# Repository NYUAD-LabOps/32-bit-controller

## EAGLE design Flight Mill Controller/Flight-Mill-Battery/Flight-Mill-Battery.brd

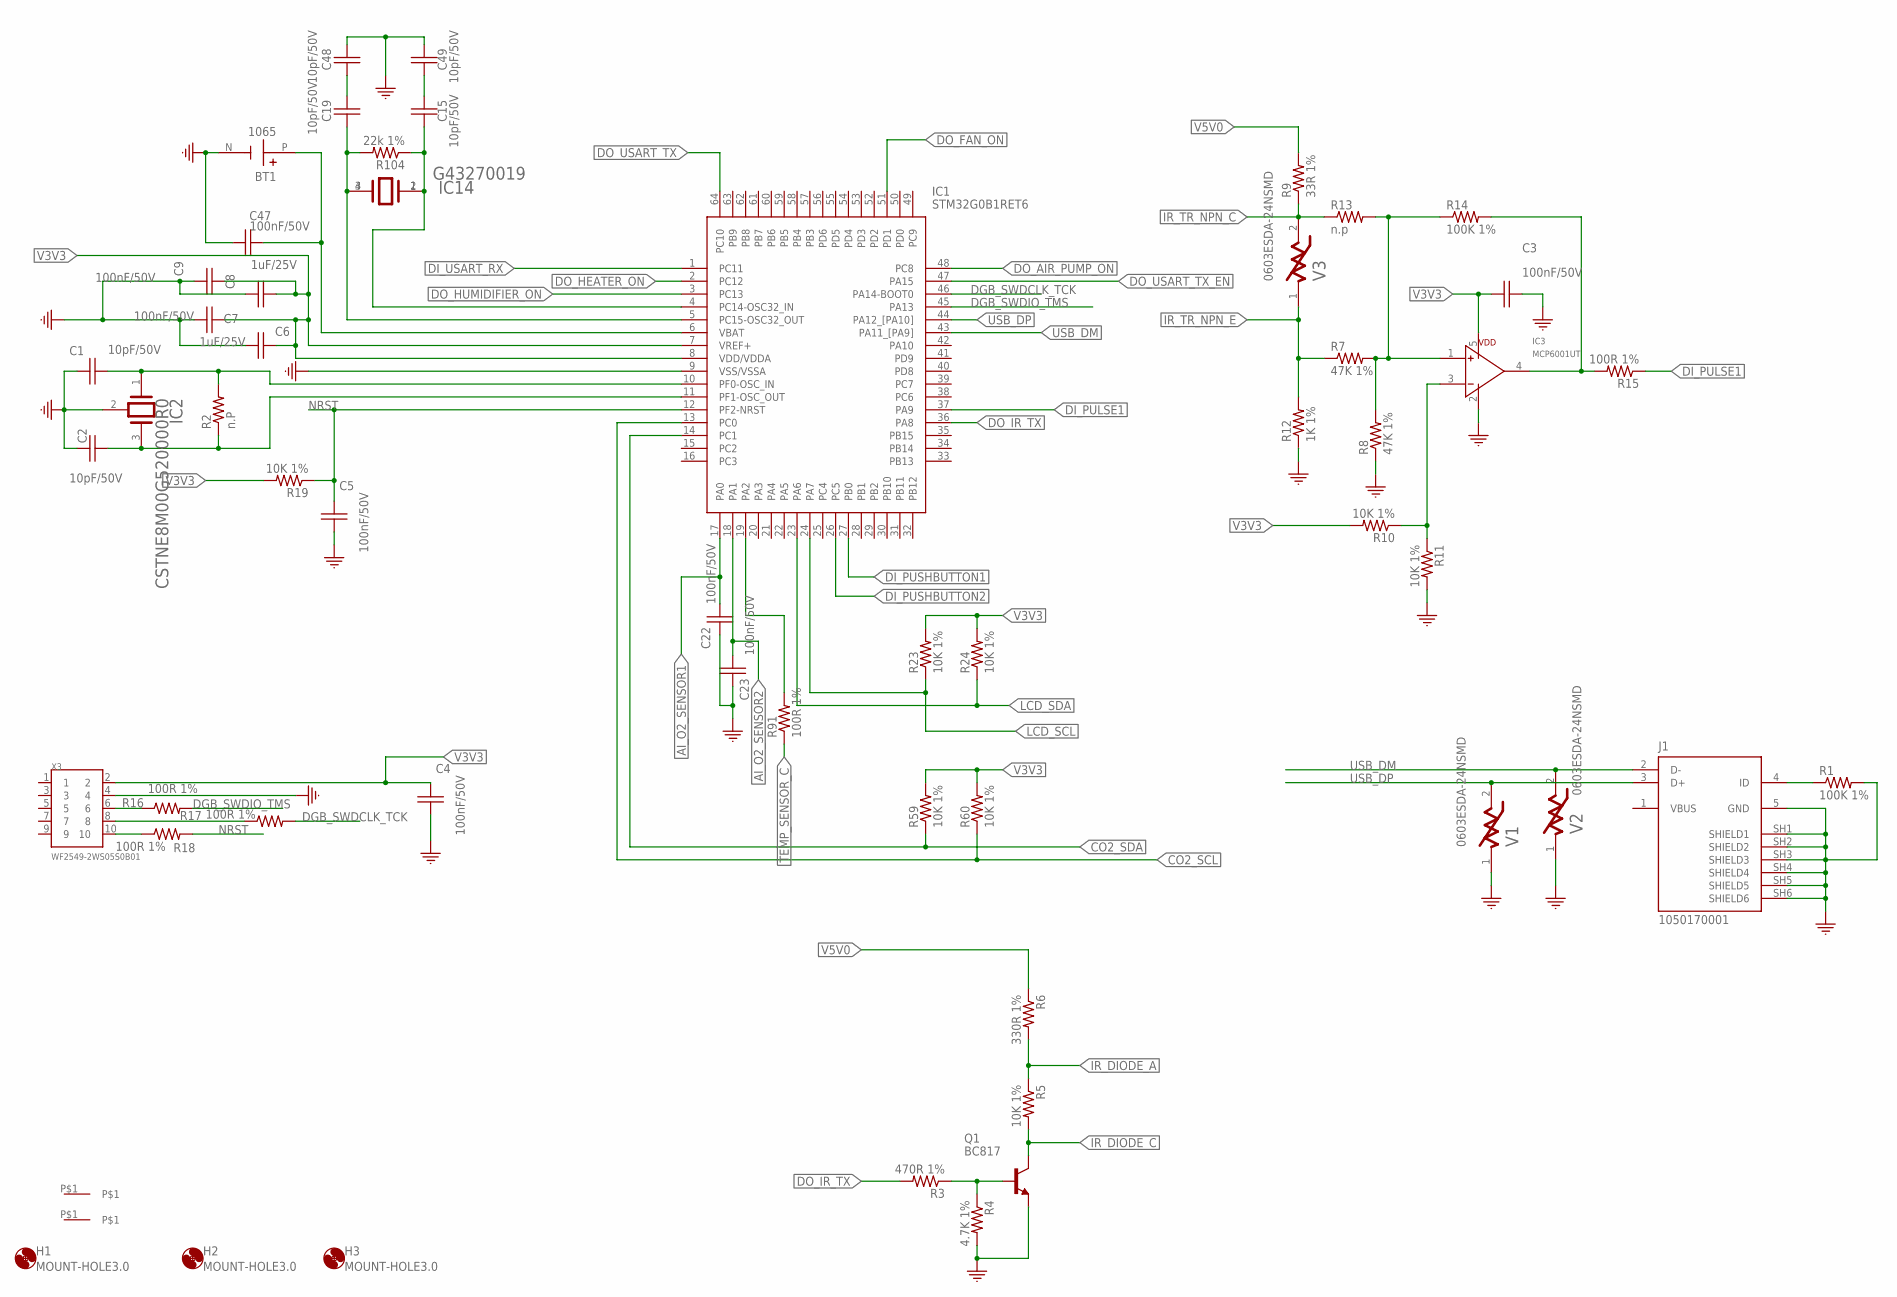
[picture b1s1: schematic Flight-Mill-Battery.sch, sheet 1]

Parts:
BT1: 1065; BAT_1065
C1, C2, C15, C19, C48, C49: 10pF/50V; EIA0603
C3, C4, C5, C7, C9, C22, C23, C47: 100nF/50V; EIA0603
C6, C8: 1uF/25V; EIA0603
FID1, FID2: FIDUCIAL
H1, H2, H3: MOUNT-HOLE3.0; 3,0
IC1: STM32G0B1RET6; QFP50P1200X1200X160-64N
IC2: CSTNE8M00G520000R0
IC3: MCP6001UT; SOT-23-5
IC14: G43270019
J1: 1050170001; MOLEX_1050170001
Q1: BC817; SOT23
R1, R14: 100K 1%; EIA0603
R2: n.P; EIA0603
R3: 470R 1%; EIA0603
R4: 4.7K 1%; EIA0603
R5, R10, R11, R19, R23, R24, R59, R60: 10K 1%; EIA0603
R6: 330R 1%; EIA0603
R7, R8: 47K 1%; EIA0603
R9: 33R 1%; EIA0603
R12: 1K 1%; EIA0603
R13: n.p; EIA0603
R15, R16, R17, R18, R91: 100R 1%; EIA0603
R104: 22k 1%; EIA0603
V1, V2, V3: 0603ESDA-24NSMD; EIA0603
X3: WF2549-2WS05S0B01; X10_100MIL_2XROW_VERT

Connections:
AI_O2_SENSOR1: C22.2, IC1.17 (PA0); also elsewhere on the board
AI_O2_SENSOR2: C23.2, IC1.18 (PA1); also elsewhere on the board
CO2_SCL: IC1.13 (PC0), R60.1; also elsewhere on the board
CO2_SDA: IC1.14 (PC1), R59.1; also elsewhere on the board
DGB_SWDCLK_TCK: IC1.46 (PA14-BOOT0), R17.2
DGB_SWDIO_TMS: IC1.45 (PA13), R16.2
DI_PULSE1: IC1.37 (PA9), R15.1
DI_PUSHBUTTON1: IC1.27 (PB0); also elsewhere on the board
DI_PUSHBUTTON2: IC1.26 (PC5); also elsewhere on the board
DI_USART_RX: IC1.1 (PC11); also elsewhere on the board
DO_AIR_PUMP_ON: IC1.48 (PC8); also elsewhere on the board
DO_FAN_ON: IC1.51 (PD1); also elsewhere on the board
DO_HEATER_ON: IC1.2 (PC12); also elsewhere on the board
DO_HUMIDIFIER_ON: IC1.3 (PC13); also elsewhere on the board
DO_IR_TX: IC1.36 (PA8), R3.2
DO_USART_TX: IC1.64 (PC10); also elsewhere on the board
DO_USART_TX_EN: IC1.47 (PA15); also elsewhere on the board
GND: BT1.N (NEG), C1.1, C2.1, C3.2, C4.1, C5.1, C6.2, C7.2, C8.2, C9.2, C22.1, C23.1, C47.2, C48.2, C49.2, IC1.9 (VSS/VSSA), IC2.2 (GND), IC3.2, J1.5 (GND), J1.SH1 (SHIELD1), J1.SH2 (SHIELD2), J1.SH3 (SHIELD3), J1.SH4 (SHIELD4), J1.SH5 (SHIELD5), J1.SH6 (SHIELD6), Q1.2 (E), R1.2, R4.2, R8.1, R11.2, R12.1, V1.1, V2.1, X3.4; also elsewhere on the board
IR_DIODE_A: R5.1, R6.2; also elsewhere on the board
IR_DIODE_C: Q1.3 (C), R5.2; also elsewhere on the board
IR_TR_NPN_C: R9.1, R13.1, V3.2; also elsewhere on the board
IR_TR_NPN_E: R7.1, R12.2, V3.1; also elsewhere on the board
LCD_SCL: IC1.24 (PA7), R23.1; also elsewhere on the board
LCD_SDA: IC1.23 (PA6), R24.1; also elsewhere on the board
unnamed: R16.1, X3.6
unnamed: C1.2, IC1.10 (PF0-OSC_IN), IC2.1 (INPUT), R2.2
unnamed: J1.4 (ID), R1.1
unnamed: C2.2, IC1.11 (PF1-OSC_OUT), IC2.3 (OUTPUT), R2.1
unnamed: IC3.1, R7.2, R8.2, R13.2, R14.1
unnamed: Q1.1 (B), R3.1, R4.1
unnamed: IC3.3, R10.1, R11.1
unnamed: IC3.4, R14.2, R15.2
unnamed: R17.1, X3.8
unnamed: R18.1, X3.10
unnamed: C19.2, C48.1
unnamed: IC1.19 (PA2), R91.2
unnamed: BT1.P (POS), C47.1, IC1.6 (VBAT)
unnamed: C19.1, IC1.5 (PC15-OSC32_OUT), IC14.3, IC14.4, R104.2
unnamed: C15.1, IC1.4 (PC14-OSC32_IN), IC14.1, IC14.2, R104.1
unnamed: C15.2, C49.1
NRST: C5.2, IC1.12 (PF2-NRST), R18.2, R19.1
TEMP_SENSOR_C: R91.1; also elsewhere on the board
USB_DM: IC1.43 (PA11_[PA9]), J1.2 (D-), V2.2
USB_DP: IC1.44 (PA12_[PA10]), J1.3 (D+), V1.2
V3V3: C3.1, C4.2, C6.1, C7.1, C8.1, C9.1, IC1.7 (VREF+), IC1.8 (VDD/VDDA), IC3.5, R10.2, R19.2, R23.2, R24.2, R59.2, R60.2, X3.2; also elsewhere on the board
V5V0: R6.1, R9.2; also elsewhere on the board
VBUS: J1.1 (VBUS)

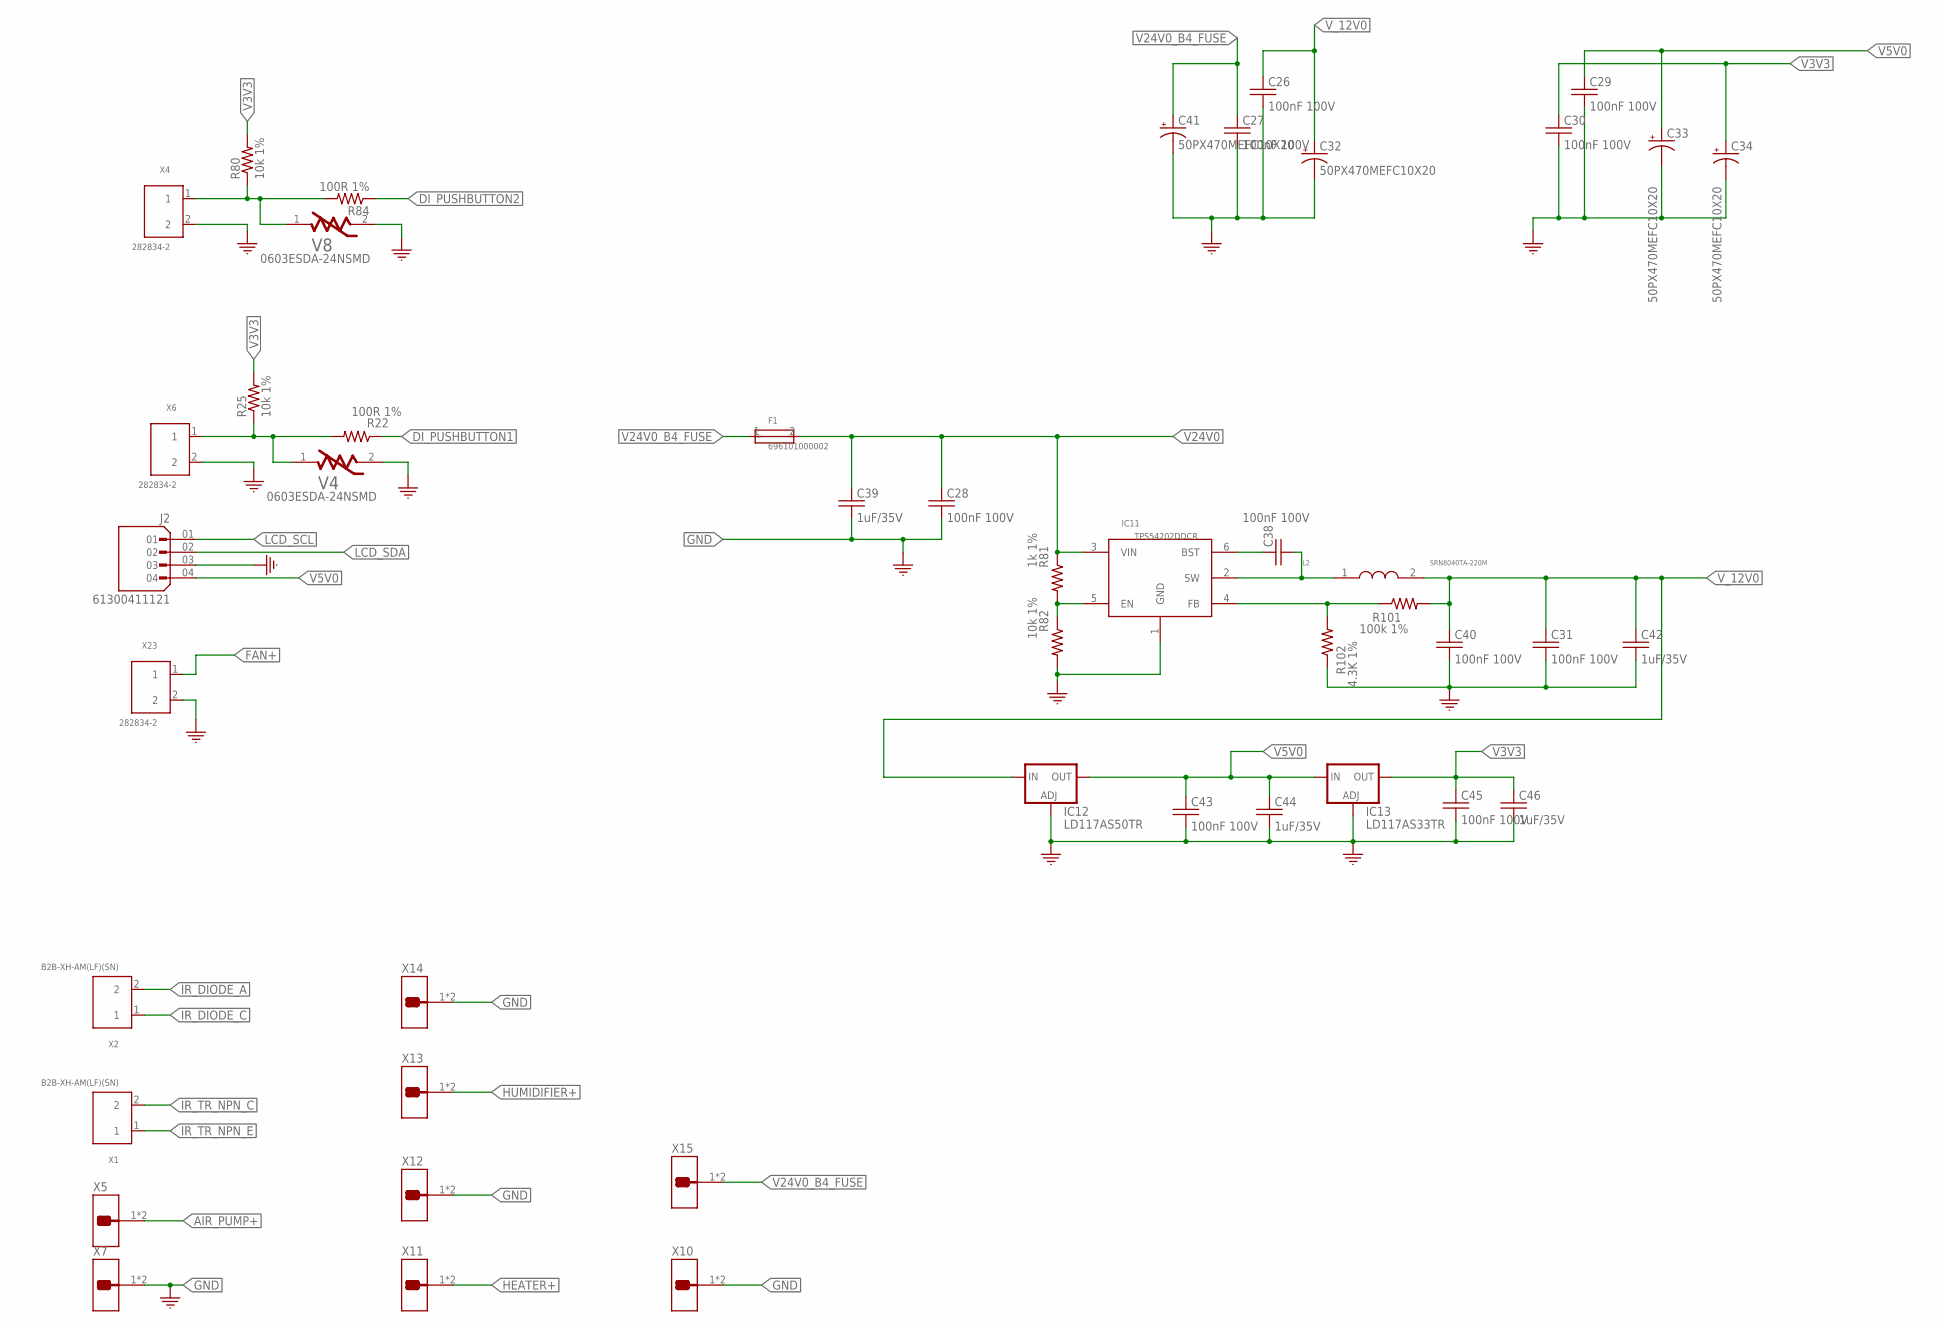
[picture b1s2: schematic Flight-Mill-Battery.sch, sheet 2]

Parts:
C26, C27, C28, C29, C30, C31, C38, C40, C43, C45: 100nF 100V; EIA0603
C32, C33, C34, C41: 50PX470MEFC10X20; CAPACITOR-ELKO-RM5-10X16
C39, C42, C44, C46: 1uF/35V; EIA0603
F1: 696101000002; FUSE_RM22.6
IC11: TPS54202DDCR; SOT23-6
IC12: LD117AS50TR; SOT223
IC13: LD117AS33TR; SOT223
J2: 61300411121; X04_100MIL_1ROW
L2: SRN8040TA-220M
R22, R84: 100R 1%; EIA0603
R25, R80, R82: 10k 1%; EIA0603
R81: 1k 1%; EIA0603
R101: 100k 1%; EIA0603
R102: 4.3K 1%; EIA0603
V4, V8: 0603ESDA-24NSMD; EIA0603
X1, X2: B2B-XH-AM(LF)(SN)
X4, X6, X23: 282834-2; TE_282834-2_0
X5, X7, X10, X11, X12, X13, X14, X15: 726386-2TE_726386-2; TE_726386-2

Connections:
AIR_PUMP+: X5.1, X5.1-2; also elsewhere on the board
DI_PUSHBUTTON1: R22.1; also elsewhere on the board
DI_PUSHBUTTON2: R84.1; also elsewhere on the board
FAN+: X23.1; also elsewhere on the board
GND: C26.2, C27.2, C28.2, C29.2, C30.2, C31.2, C32.2 (-), C33.2 (-), C34.2 (-), C39.2, C40.2, C41.2 (-), C42.2, C43.2, C44.2, C45.2, C46.2, IC11.1 (GND), IC12.1 (ADJ), IC13.1 (ADJ), J2.03, R82.2, R102.1, V4.2, V8.2, X4.2, X6.2, X7.1, X7.1-2, X10.1, X10.1-2, X12.1, X12.1-2, X14.1, X14.1-2, X23.2; also elsewhere on the board
HEATER+: X11.1, X11.1-2; also elsewhere on the board
HUMIDIFIER+: X13.1, X13.1-2; also elsewhere on the board
IR_DIODE_A: X2.2; also elsewhere on the board
IR_DIODE_C: X2.1; also elsewhere on the board
IR_TR_NPN_C: X1.2; also elsewhere on the board
IR_TR_NPN_E: X1.1; also elsewhere on the board
LCD_SCL: J2.01; also elsewhere on the board
LCD_SDA: J2.02; also elsewhere on the board
unnamed: IC11.5 (EN), R81.2, R82.1
unnamed: R22.2, R25.1, V4.1, X6.1
unnamed: R80.1, R84.2, V8.1, X4.1
unnamed: C38.1, IC11.6 (BST)
unnamed: C38.2, IC11.2 (SW), L2.1
unnamed: IC11.4 (FB), R101.1, R102.2
V3V3: C30.1, C34.1 (+), C45.1, C46.1, IC13.4 (OUT), R25.2, R80.2; also elsewhere on the board
V5V0: C29.1, C33.1 (+), C43.1, C44.1, IC12.4 (OUT), IC13.3 (IN), J2.04; also elsewhere on the board
V24V0: C28.1, C39.1, F1.2, IC11.3 (VIN), R81.1; also elsewhere on the board
V24V0_B4_FUSE: C27.1, C41.1 (+), F1.1, X15.1, X15.1-2
V_12V0: C26.1, C31.1, C32.1 (+), C40.1, C42.1, IC12.3 (IN), L2.2, R101.2; also elsewhere on the board

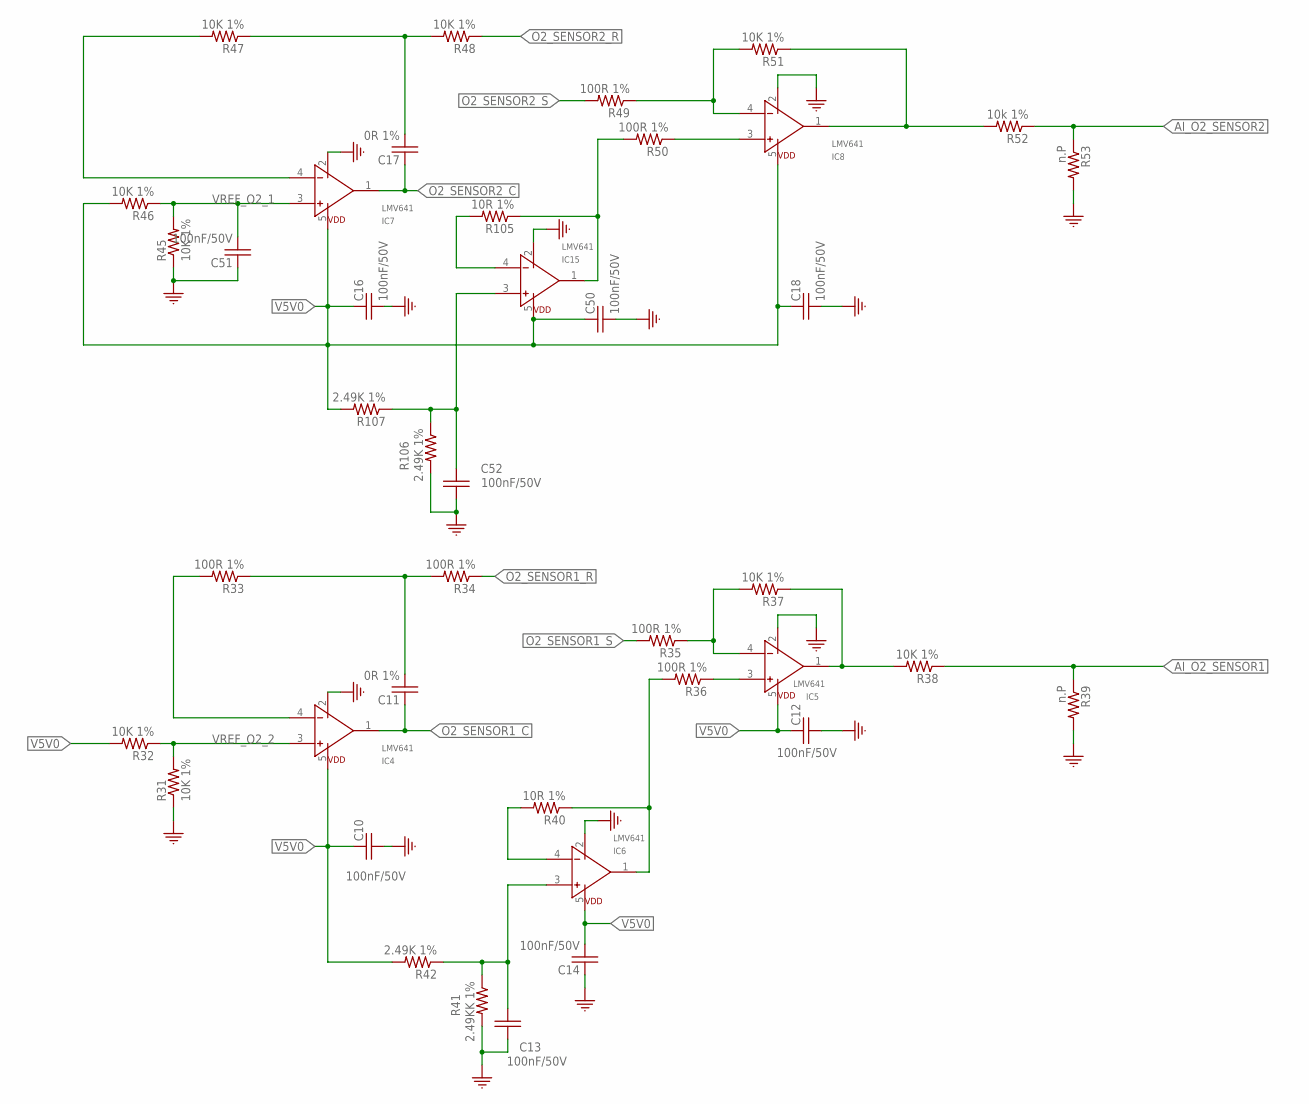
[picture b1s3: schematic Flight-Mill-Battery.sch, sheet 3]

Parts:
C10, C12, C13, C14, C16, C18, C50, C51, C52: 100nF/50V; EIA0603
C11, C17: 0R 1%; EIA0603
IC4, IC5, IC6, IC7, IC8, IC15: LMV641; SOT-23-5
R31, R32, R37, R38, R45, R46, R47, R48, R51: 10K 1%; EIA0603
R33, R34, R35, R36, R49, R50: 100R 1%; EIA0603
R39, R53: n.P; EIA0603
R40, R105: 10R 1%; EIA0603
R41: 2.49KK 1%; EIA0603
R42, R106, R107: 2.49K 1%; EIA0603
R52: 10k 1%; EIA0603

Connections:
AI_O2_SENSOR: IC5.1 (OUT), R37.1, R38.2
AI_O2_SENSOR1: R38.1, R39.1; also elsewhere on the board
AI_O2_SENSOR2: R52.1, R53.1; also elsewhere on the board
GND: C10.2, C12.2, C13.1, C14.1, C16.2, C18.2, C50.2, C51.1, C52.1, IC4.2 (VEE), IC5.2 (VEE), IC6.2 (VEE), IC7.2 (VEE), IC8.2 (VEE), IC15.2 (VEE), R31.1, R39.2, R41.2, R45.1, R53.2, R106.2; also elsewhere on the board
unnamed: IC5.4 (IN-), R35.1, R37.2
unnamed: IC6.4 (IN-), R40.2
unnamed: C11.2, R33.1, R34.2
unnamed: IC4.4 (IN-), R33.2
unnamed: IC6.1 (OUT), R36.2, R40.1
unnamed: IC5.3 (IN+), R36.1
unnamed: C13.2, IC6.3 (IN+), R41.1, R42.1
unnamed: C17.2, R47.1, R48.2
unnamed: IC7.4 (IN-), R47.2
unnamed: IC8.4 (IN-), R49.1, R51.2
unnamed: C52.2, IC15.3 (IN+), R106.1, R107.1
unnamed: IC8.1 (OUT), R51.1, R52.2
unnamed: IC15.4 (IN-), R105.2
unnamed: IC15.1 (OUT), R50.2, R105.1
unnamed: IC8.3 (IN+), R50.1
O2_SENSOR1_C: C11.1, IC4.1 (OUT); also elsewhere on the board
O2_SENSOR1_R: R34.1; also elsewhere on the board
O2_SENSOR1_S: R35.2; also elsewhere on the board
O2_SENSOR2_C: C17.1, IC7.1 (OUT); also elsewhere on the board
O2_SENSOR2_R: R48.1; also elsewhere on the board
O2_SENSOR2_S: R49.2; also elsewhere on the board
V5V0: C10.1, C12.1, C14.2, C16.1, C18.1, C50.1, IC4.5 (VCC), IC5.5 (VCC), IC6.5 (VCC), IC7.5 (VCC), IC8.5 (VCC), IC15.5 (VCC), R32.2, R42.2, R46.2, R107.2; also elsewhere on the board
VREF_O2_1: C51.2, IC7.3 (IN+), R45.2, R46.1
VREF_O2_2: IC4.3 (IN+), R31.2, R32.1

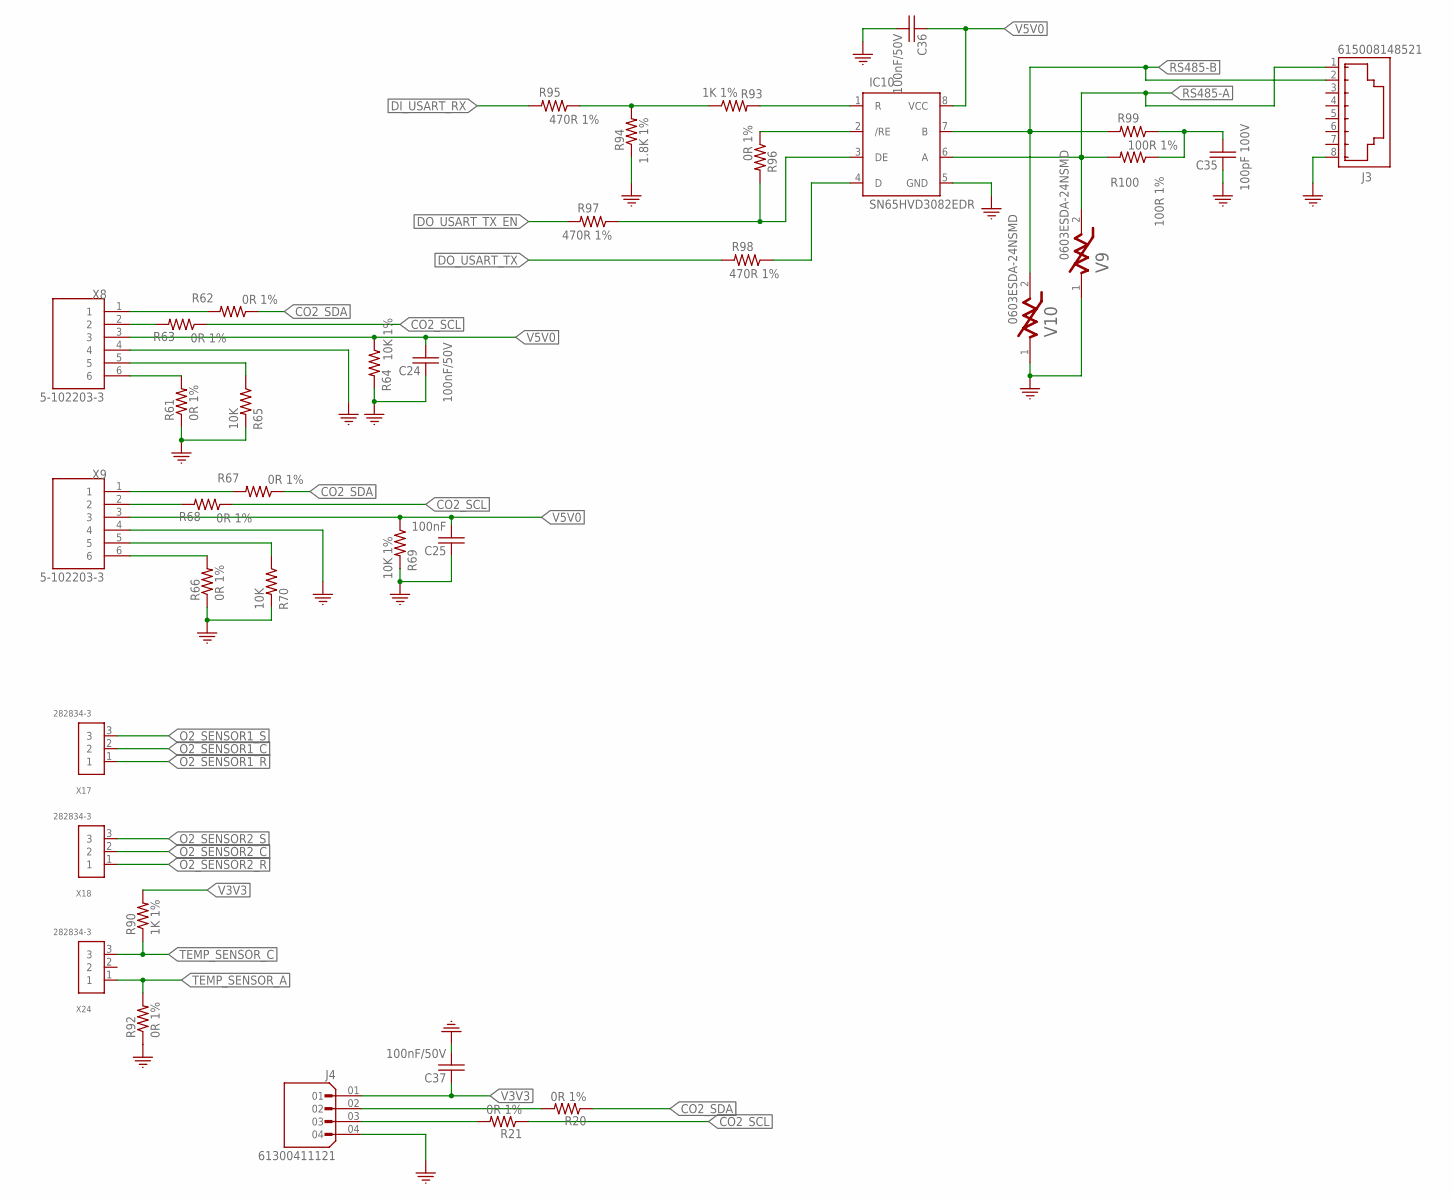
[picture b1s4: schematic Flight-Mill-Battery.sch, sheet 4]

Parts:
C24, C36, C37: 100nF/50V; EIA0603
C25: 100nF; EIA0603
C35: 100pF 100V; EIA0603
IC10: SN65HVD3082EDR; SOIC8
J3: 615008148521
J4: 61300411121; X04_100MIL_1ROW
R20, R21, R61, R62, R63, R66, R67, R68, R92, R96: 0R 1%; EIA0603
R64, R69: 10K 1%; EIA0603
R65, R70: 10K; EIA0603
R90, R93: 1K 1%; EIA0603
R94: 1.8K 1%; EIA0603
R95, R97, R98: 470R 1%; EIA0603
R99, R100: 100R 1%; EIA0603
V9, V10: 0603ESDA-24NSMD; EIA0603
X8, X9: 5-102203-3; TE_5-102203-3
X17, X18, X24: 282834-3; TE_282834-3_0

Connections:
CO2_SCL: R21.1, R63.1, R68.1; also elsewhere on the board
CO2_SDA: R20.1, R62.1, R67.1; also elsewhere on the board
DI_USART_RX: R95.2; also elsewhere on the board
DO_USART_TX: R98.2; also elsewhere on the board
DO_USART_TX_EN: R97.2; also elsewhere on the board
GND: C24.1, C25.1, C35.1, C36.2, C37.2, IC10.5 (GND), J3.8, J4.04, R61.1, R64.2, R65.2, R66.1, R69.2, R70.2, R92.1, R94.1, V9.1, V10.1, X8.4, X9.4; also elsewhere on the board
unnamed: R61.2, X8.6
unnamed: R62.2, X8.1
unnamed: R63.2, X8.2
unnamed: R65.1, X8.5
unnamed: R66.2, X9.6
unnamed: R67.2, X9.1
unnamed: R68.2, X9.2
unnamed: R70.1, X9.5
unnamed: R93.1, R94.2, R95.1
unnamed: IC10.1 (R), R93.2
unnamed: IC10.2 (/RE), R96.1
unnamed: IC10.3 (DE), R96.2, R97.1
unnamed: IC10.4 (D), R98.1
unnamed: J4.02, R20.2
unnamed: J4.03, R21.2
unnamed: C35.2, R99.1, R100.1
O2_SENSOR1_C: X17.2; also elsewhere on the board
O2_SENSOR1_R: X17.1; also elsewhere on the board
O2_SENSOR1_S: X17.3; also elsewhere on the board
O2_SENSOR2_C: X18.2; also elsewhere on the board
O2_SENSOR2_R: X18.1; also elsewhere on the board
O2_SENSOR2_S: X18.3; also elsewhere on the board
RS485-A: IC10.6 (A), J3.1, R100.2, V9.2
RS485-B: IC10.7 (B), J3.2, R99.2, V10.2
TEMP_SENSOR_A: R92.2, X24.1
TEMP_SENSOR_C: R90.1, X24.3; also elsewhere on the board
V3V3: C37.1, J4.01, R90.2; also elsewhere on the board
V5V0: C24.2, C25.2, C36.1, IC10.8 (VCC), R64.1, R69.1, X8.3, X9.3; also elsewhere on the board

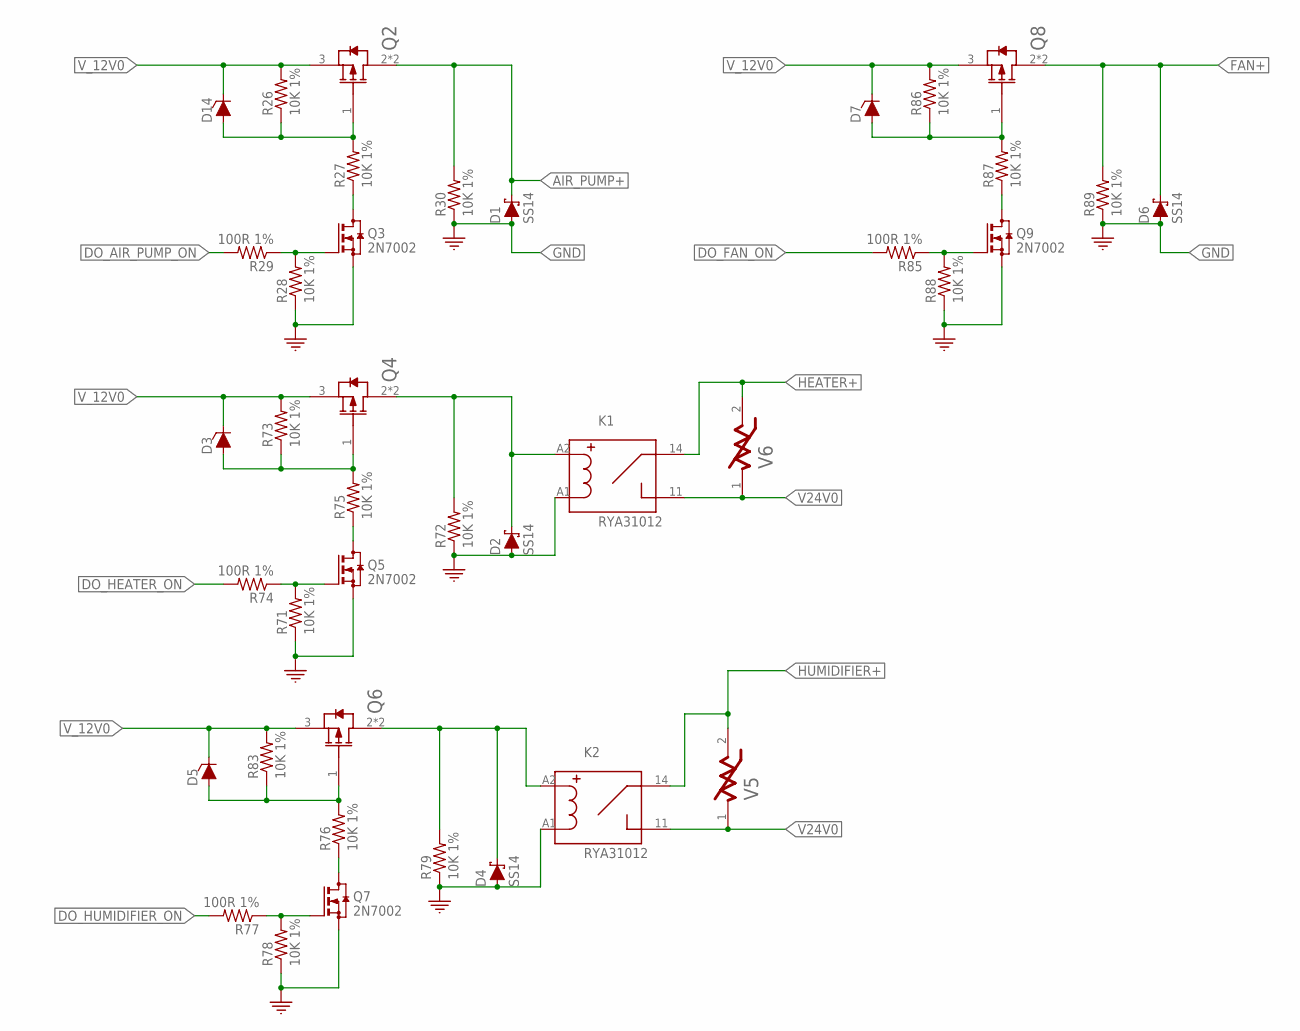
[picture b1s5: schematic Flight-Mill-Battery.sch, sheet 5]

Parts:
D1, D2, D4, D6: SS14; SMA
D3, D5, D7, D14: MMBZ4696-HE3-18; SOT23-3
K1, K2: RYA31012
Q2, Q4, Q6, Q8: UT2955G-AA3-R; SOT223
Q3, Q5, Q7, Q9: 2N7002; SOT23
R26, R27, R28, R30, R71, R72, R73, R75, R76, R78, R79, R83, R86, R87, R88, R89: 10K 1%; EIA0603
R29, R74, R77, R85: 100R 1%; EIA0603
V5, V6: B72205S0271K101B72205S2131K101; EPCOS_B72205S0271K101_0

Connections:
AIR_PUMP+: D1.1 (C), Q2.2 (DRAIN), Q2.4 (DRAIN), R30.2; also elsewhere on the board
DO_AIR_PUMP_ON: R29.2; also elsewhere on the board
DO_FAN_ON: R85.2; also elsewhere on the board
DO_HEATER_ON: R74.2; also elsewhere on the board
DO_HUMIDIFIER_ON: R77.2; also elsewhere on the board
FAN+: D6.1 (C), Q8.2 (DRAIN), Q8.4 (DRAIN), R89.2; also elsewhere on the board
GND: D1.2 (A), D2.2 (A), D4.2 (A), D6.2 (A), K1.A1 (1), K2.A1 (1), Q3.2 (S), Q5.2 (S), Q7.2 (S), Q9.2 (S), R28.1, R30.1, R71.1, R72.1, R78.1, R79.1, R88.1, R89.1; also elsewhere on the board
HEATER+: K1.14 (3), V6.2; also elsewhere on the board
HUMIDIFIER+: K2.14 (3), V5.2; also elsewhere on the board
unnamed: D14.1 (A), Q2.1 (GATE), R26.1, R27.2
unnamed: Q3.3 (D), R27.1
unnamed: Q3.1 (G), R28.2, R29.1
unnamed: D3.1 (A), Q4.1 (GATE), R73.1, R75.2
unnamed: Q5.3 (D), R75.1
unnamed: Q5.1 (G), R71.2, R74.1
unnamed: D5.1 (A), Q6.1 (GATE), R76.2, R83.1
unnamed: Q7.3 (D), R76.1
unnamed: Q7.1 (G), R77.1, R78.2
unnamed: D4.1 (C), K2.A2 (2), Q6.2 (DRAIN), Q6.4 (DRAIN), R79.2
unnamed: D2.1 (C), K1.A2 (2), Q4.2 (DRAIN), Q4.4 (DRAIN), R72.2
unnamed: D7.1 (A), Q8.1 (GATE), R86.1, R87.2
unnamed: Q9.3 (D), R87.1
unnamed: Q9.1 (G), R85.1, R88.2
V24V0: K1.11 (4), K2.11 (4), V5.1, V6.1; also elsewhere on the board
V_12V0: D3.3 (C), D5.3 (C), D7.3 (C), D14.3 (C), Q2.3 (SOURCE), Q4.3 (SOURCE), Q6.3 (SOURCE), Q8.3 (SOURCE), R26.2, R73.2, R83.2, R86.2; also elsewhere on the board

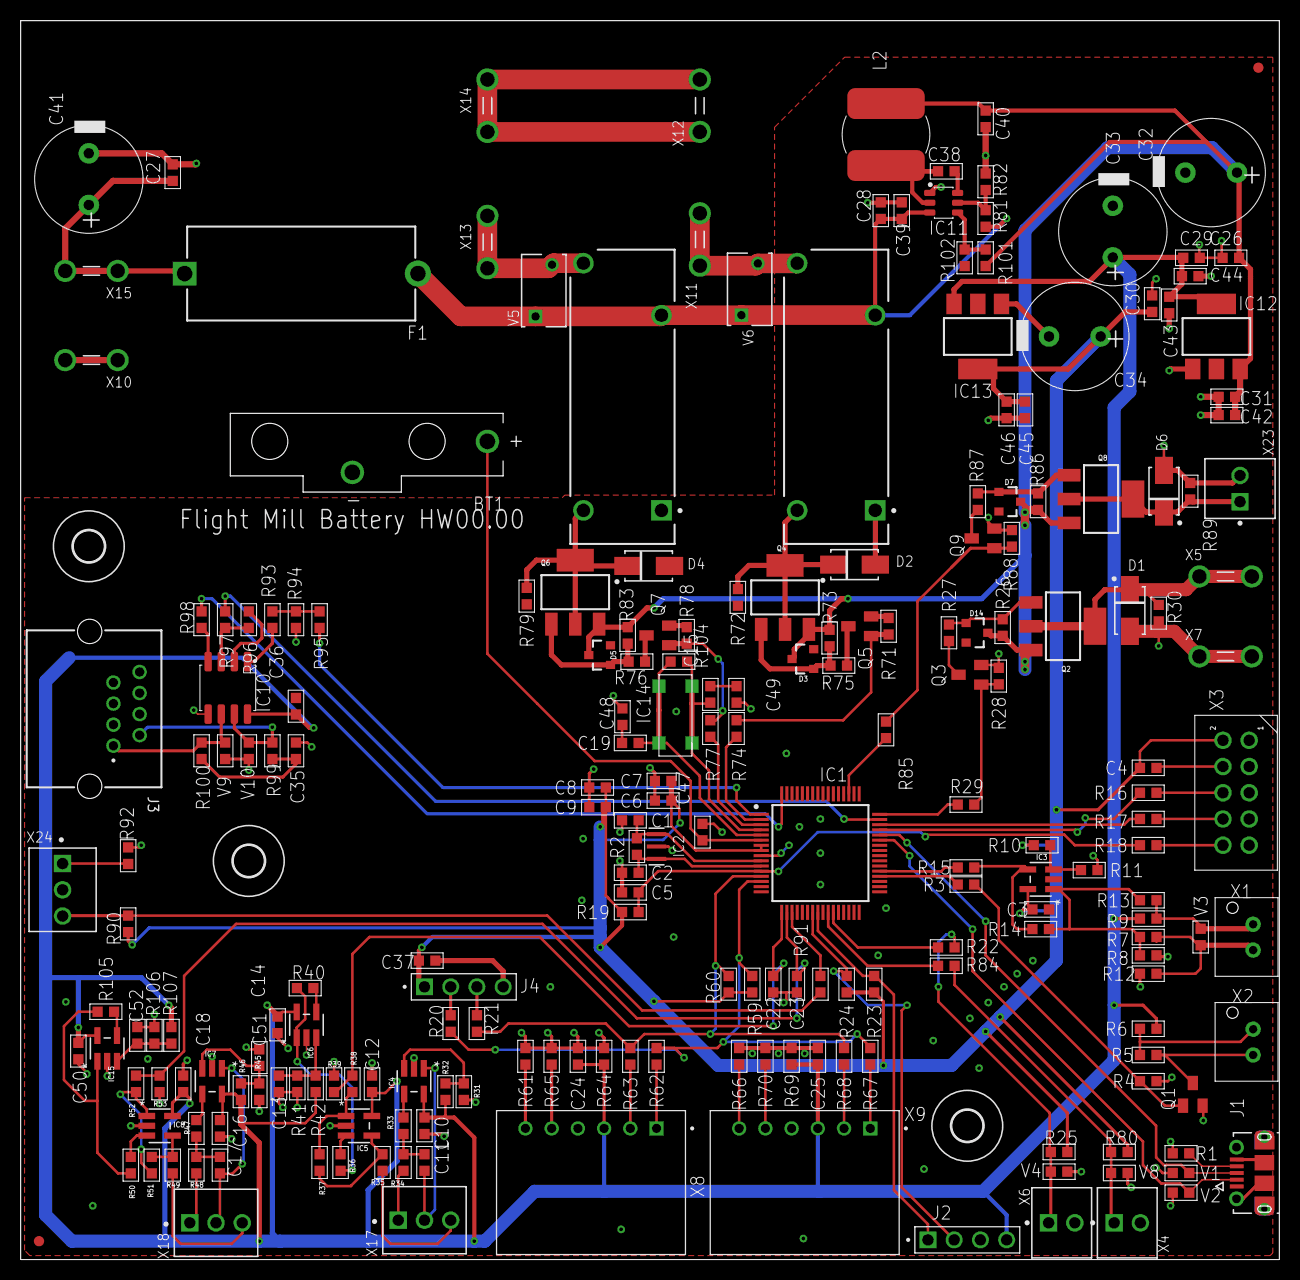
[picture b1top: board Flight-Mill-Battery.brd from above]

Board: 2 copper layers, 121.9 x 120.0 mm, 222 parts (0 on the bottom side), 116 nets.

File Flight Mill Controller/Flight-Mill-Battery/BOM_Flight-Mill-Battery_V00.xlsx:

Qty | Value | Device | Package | Parts | DESCRIPTION | MFN | MFR
1 |  | C_0603EIA0603 | EIA0603 | C25
7 | 0603ESDA-24NSMD | 0603ESDA-24NSMD | EIA0603 | V1, V2, V3, V4, V8, V9, V10 | aristor 0603 SMD Bidirectional 50V 24V | 0603ESDA-24N | Bourns
11 | 0R 1% | R_0603 | EIA0603 | R20, R21, R61, R62, R63, R66, R67, R68, R92, R96, R103 |  | Open Source 0603
2 | 1.5K 1% | R_0603 | EIA0603 | R41, R106 |  | Open Source 0603
1 | 1.8K 1% | R_0603 | EIA0603 | R94 |  | Open Source 0603
1 | 100K 1% | R_0603 | EIA0603 | R1 |  | Open Source 0603
18 | 100R 1% | R_0603 | EIA0603 | R15, R16, R17, R18, R22, R29, R35, R36, R49, R50, R52, R74, R77, R84, R85, R91,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 |  | Open Source 0603
1 | 100k 1% | R_0603 | EIA0603 | R101 |  | Open Source 0603
10 | 100nF 100V | C_0603EIA0603 | EIA0603 | C26, C27, C28, C29, C30, C31, C38, C40, C43, C45
22 | 100nF/50V | C_0603EIA0603 | EIA0603 | C3, C4, C5, C7, C9, C10, C11, C12, C13, C14, C16, C17, C18, C22, C23, C24, C36,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
1 | 100pF 100V | C_0603EIA0603 | EIA0603 | C35
1 | 1050170001 | 1050170001 | MOLEX_1050170001 | J1 | USB - micro B USB 2.0 Receptacle Connector 5 Position Surface Mount, Right Angle
1 | 1065 | 1065 | BAT_1065 | BT1 | Coin Battery Holder 20mm Cell-Vertical CR2032
2 | 10K | R_0603 | EIA0603 | R65, R70 |  | Open Source 0603
35 | 10K 1% | R_0603 | EIA0603 | R5, R10, R11, R19, R23, R24, R26, R27, R28, R30, R31, R32, R33, R34, R38, R45, 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 |  | Open Source 0603
2 | 10R 1% | R_0603 | EIA0603 | R40, R105 |  | Open Source 0603
3 | 10k 1% | R_0603 | EIA0603 | R25, R80, R82 |  | Open Source 0603
4 | 10pF/50V | C_0603EIA0603 | EIA0603 | C1, C2, C48, C49
3 | 1K 1% | R_0603 | EIA0603 | R12, R90, R93 |  | Open Source 0603
1 | 1k 1% | R_0603 | EIA0603 | R81 |  | Open Source 0603
2 | 1uF/25V | C_0603EIA0603 | EIA0603 | C6, C8
4 | 1uF/35V | C_0603EIA0603 | EIA0603 | C39, C42, C44, C46
2 | 2.49K 1% | R_0603 | EIA0603 | R42, R107 |  | Open Source 0603
2 | 22K 1% | R_0603 | EIA0603 | R37, R51 |  | Open Source 0603
1 | 22k 1% | R_0603 | EIA0603 | R104 |  | Open Source 0603
3 | 282834-2 | 282834-2 | TE_282834-2_0 | X4, X6, X23 | Connector Header Terminal Block 2 Positions, 1 Row, 2.54mm, THT | 282834-2 | TE
3 | 282834-3 | 282834-3 | TE_282834-3_0 | X17, X18, X24 | Connector 3 Position THT 1 Row 2.54mm pitch side entry wire to board | 282834-3 | TE
4 | 2N7002 | 2N7002 | SOT23 | Q3, Q5, Q7, Q9 | NMOSFET, 500mA, 60V, Vth 2.5V | 2N7002 | Diodes, Guangdong Hotetech,NXP
2 | 330R 1% | R_0603 | EIA0603 | R6, R9 |  | Open Source 0603
1 | 4.3K 1% | R_0603 | EIA0603 | R102 |  | Open Source 0603
1 | 4.7K 1% | R_0603 | EIA0603 | R4 |  | Open Source 0603
4 | 470R 1% | R_0603 | EIA0603 | R3, R95, R97, R98 |  | Open Source 0603
3 | 47K 1% | R_0603 | EIA0603 | R7, R8, R14 |  | Open Source 0603
2 | 5-102203-3 | 5-102203-3 | TE_5-102203-3 | X8, X9 | PCB Header, Right Angle, Shrouded, 06 HDR SRRA SHRD LF, AMPMODU Mod II Series |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 | 5-102203-3 | TE Connectivity
4 | 50PX470MEFC10X20 | 50PX470MEFC10X20 | CAPACITOR-ELKO-RM5-10X16 | C32, C33, C34, C41 | 470uF ±20% 50V 10mm 20mm 5mm 2000Hrs @ 105℃ -55℃ ~ +105℃ | 50PX470MEFC10X20 | Rubicon
2 | 61300411121 | 61300411121 | X04_100MIL_1ROW | J2, J4 | Connector Header Through Hole 4 position 0.100 (2.54mm) | 61300411121 | Wurth Electronics
1 | 615008148521 | 615008148521 | 615008148521 | J3 | RJ45 unshielded 8P8C | 615008148521 | Wurth Elektronik
1 | 696101000002 | 696101000002 | FUSE_RM22.6 | F1 | Fuse Block 10 A 250V 1 Circuit Cartridge Through Hole | 696101000002 | Wurth Elektronik
8 | 726386-2TE_726386-2 | 726386-2TE_726386-2 | TE_726386-2 | X5, X7, X10, X11, X12, X13, X14, X15
2 | B2B-XH-AM(LF)(SN) | B2B-XH-AM(LF)(SN) | B2B-XH-AM(LF)(SN) | X1, X2 | Connector, 2 pins, Header THT , Pitch 2.5mm, JST, Vertical | B2B-XH-AM(LF)(SN) | JST
2 | B72205S0271K101B72205S2131K101 | B72205S0271K101B72205S2131K101 | EPCOS_B72205S0271K101_0 | V5, V6 |  | B72205S0271K1011 | EPCOS
1 | BC817 | BC817 | SOT23 | Q1 | Transistor BJT NPN SOT23 45V 0.5A | BC817 | NXP
1 | CSTNE8M00G520000R0 | CSTNE8M00G520000R0 | CSTNE8M00G520000R0 | IC2 | 8MHz ±0.5% 10pF 40Ω SMD3213-3P Ceramic Resonators | CSTNE8M00G520000R0 | Murata
2 | FIDUCIAL | FIDUCIAL | FIDUCIAL | FID1, FID2
1 | G43270019 | G43270019 | G43270019 | IC14 | Crystals 32.768kHz 12.5pF 20ppm -40 +85 | G43270019 | Diodes Inc
1 | LD117AS33TR | LD117AS33TR | SOT223 | IC13
1 | LD117AS50TR | LD117AS50TR | SOT223 | IC12
6 | LMV641 | LMV641 | SOT-23-5 | IC4, IC5, IC6, IC7, IC8, IC15 | 1CH 10MHz 1 Low power 2.3 V/us 2.7V~12V SOT-23-5 OpAmp | LMV641MF/NOPB | Texas Instruments
1 | MCP6001UT | MCP6001UT | SOT-23-5 | IC3
4 | MMBZ4696-HE3-18 | MMBZ4696-HE3-18 | SOT23-3 | D3, D5, D7, D14 | Zener Diodes 9.1 Volt 0.225W 5% AUTO | MMBZ4696-HE3-18 | Vishay
3 | MOUNT-HOLE3.0 | MOUNT-HOLE3.0 | 3,0 | H1, H2, H3
2 | RYA31012 | RYA31012 | RYA31012 | K1, K2 | 5A Relay 12V, SPST NO (1Form A) | RYA31012 | TE Connectivity
1 | SN65HVD3082EDR | SN65HVD3082EDR | SOIC8 | IC10 | RS485 Transciever, 200Kbps, SOIC-8 , ALT: TP8485E-SR (3Peak) | SN65HVD3082EDR | TI,3Peak
1 | SRN8040TA-220M | SRN8040TA-220M | SRN8040TA-220M | L2 | FIXED IND 22UH 2.9A SMD, 73m-Ohm, Bourns | SRN8040TA-220M | Bourns
4 | SS14 | SS14 | SMA | D1, D2, D4, D6 | Diode Schottky 1A/40V (SMA) | SS14-LTP | MCC
1 | STM32G0B1RET6 | STM32G0B1RET6 | QFP50P1200X1200X160-64N | IC1 | Mainstream Arm Cortex-M0+ 32-bit MCU, up to 512KB Flash, 144KB RAM, 6x USART, t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
1 | TPS54202DDCR | TPS54202DDCR | SOT23-6 | IC11 | 2A 28V SOT-23-6 Sync Buck | TPS54202DDCR | Texas Instruments
4 | UT2955G-AA3-R | UT2955G-AA3-R | SOT223 | Q2, Q4, Q6, Q8 |  | UT2955G-AA3-R | UTC
1 | WF2549-2WS05S0B01 | WF2549-2WS05S0B01 | X10_100MIL_2XROW_VERT | X3 | X10, 10 Pins, Header, Pitch 2.54 wire to board 2xrows, THT | WF2549-2WS05S0B01 | WCON
3 | n.P | R_0603 | EIA0603 | R2, R39, R53 |  | Open Source 0603
1 | n.p | R_0603 | EIA0603 | R13 |  | Open Source 0603

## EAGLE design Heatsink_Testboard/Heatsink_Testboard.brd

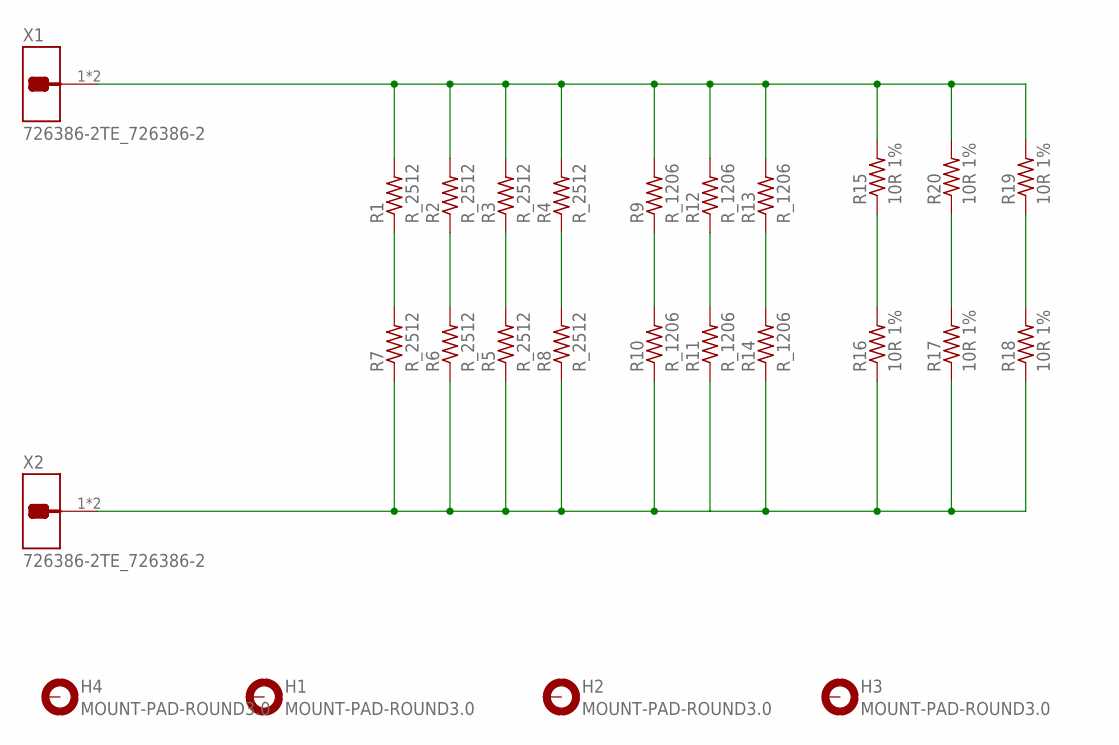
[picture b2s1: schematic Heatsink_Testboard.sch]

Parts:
H1, H2, H3, H4: MOUNT-PAD-ROUND3.0; 3,0-PAD
R1, R2, R3, R4, R5, R6, R7, R8: R_2512; EIA2512
R9, R10, R11, R12, R13, R14: R_1206; R1206
R15, R16, R17, R18, R19, R20: 10R 1%; EIA0603
X1, X2: 726386-2TE_726386-2; TE_726386-2

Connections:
BATT+: R1.2, R2.2, R3.2, R4.2, R9.2, R12.2, R13.2, R15.2, R19.2, R20.2, X1.1, X1.1-2
BATT-: R5.1, R6.1, R7.1, R8.1, R10.1, R11.1, R14.1, R16.1, R17.1, R18.1, X2.1, X2.1-2
unnamed: R11.2, R12.1
unnamed: R9.1, R10.2
unnamed: R4.1, R8.2
unnamed: R3.1, R5.2
unnamed: R2.1, R6.2
unnamed: R1.1, R7.2
unnamed: R13.1, R14.2
unnamed: R15.1, R16.2
unnamed: R17.2, R20.1
unnamed: R18.2, R19.1

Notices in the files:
parts and their libraries:
COPYRIGHT: Copyright (C) 2023 Ultra Librarian. All rights reserved.
